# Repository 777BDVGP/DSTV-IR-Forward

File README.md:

# IR Forward — DSTV remote control in another room

Use your DSTV remote in a bedroom while the decoder is in another room. A
small board in the bedroom picks up the remote's infrared signal and sends it
over WiFi (ESP-NOW, board to board) to a board at the decoder, which sends it
out again on an infrared LED in front of the decoder.

**Project page:** https://zanaz.co.za/project-irforward.html — photos, build guide,
downloads and a contact form for questions.

### Why this project: only DSTV gets through

There are many ways to carry infrared from one room to another — IR repeaters,
"remote extenders", smart IR blasters. They pass on **every** infrared signal
they see. In a house with several TVs, sound bars and air conditioners that is
a problem: the bedroom TV remote also switches the lounge TV of the same
brand, the bedroom sound bar remote changes the lounge sound bar's volume, and
so on.

**This system deliberately blocks every remote except the DSTV remote.**

- The sender decodes each infrared signal it receives. Only signals in the
  **DSTV protocol (XMP)** are passed on; everything else — TV, sound bar,
  aircon, other set-top boxes — is ignored. The LEDs show it: **green** = DSTV
  code forwarded, **red** = other remote, ignored.
- The receiver does not replay a recording of the signal: it **rebuilds the
  DSTV code with exact timing**, so the decoder gets a clean signal even when
  the bedroom reception was weak.
- Result: you can use all your remotes normally in every room, and only the
  DSTV decoder reacts to the bedroom DSTV remote.
- Not DStv? The sender can **learn another TV box's remote** instead — see
  *Another TV box*.

The only exception is on purpose and temporary: while you **record an IR
sequence** from a sender's web page, that sender also passes on other remotes,
so you can see on the receiver's side that the recorded button works.

Extras on the receiver: record **IR sequences** from any remote (TV, sound
bar, DSTV), add known codes (e.g. Samsung TV Power ON / OFF), and run them on a
**weekly schedule** — for example a daily "reset" of TV, decoder and sound bar.

| Folder | Firmware | Where the board goes |
|---|---|---|
| `TV_IR_Sending` | **Sender (TX)** — one per room with a remote | in the room, IR receiver facing the remote |
| `TV_IR_Receiving` | **Receiver (RX)** — one per decoder | at the decoder, IR LED pointed at it |
| `TV_IR_IN_ONE` | **All-in-One** — sender and receiver on one board | when the remote's room and the decoder are next to each other (IR LED wired through) |

All three run on the same PCB (`PCB/IR_FORWARD_V1`), with a WEMOS LOLIN S2 Mini
(ESP32-S2). Printable enclosure parts (.stl: case, lid, IR clip, LED holders)
are in `Enclosure/`; the PCB (schematic, board, Gerber zip) is in `PCB/`.

**Firmware on a new board in 2 minutes, from the browser** — the normal way,
no software to install: https://777bdvgp.github.io/DSTV-IR-Forward/ (Chrome or
Edge) — see step 6 below.

## Building one, step by step

### 1. Order the PCB

Upload `PCB/IR_FORWARD_V1_2026-10-04.zip` (the Gerber files) to [PCBWay](https://www.pcbway.com/)
— I have my own boards made there and can recommend them: easy to order, good quality and
quick delivery — or any other PCB maker: 2 layers, 1.6 mm, default settings. The same PCB is
used for the sender, the receiver and the All-in-One. The Eagle schematic and
board are in `PCB/` (also as `SCHEMATIC.jpg` and `PCB.jpg`).

The finished PCB (S2 Mini not plugged in):

The **WEMOS LOLIN S2 Mini** (ESP32-S2) that plugs onto it — purple, with a
USB-C plug and the two buttons **0** (left) and **RST** (right) that you need
to put the firmware on it (step 6):

### 2. Parts on the PCB

| Qty | Part | Value / type | Silkscreen |
|---|---|---|---|
| 1 | WEMOS LOLIN **S2 Mini** (ESP32-S2) + 2 × **female** headers | plugs onto the two double pin rows | WEMOS MINI |
| 1 | AC/DC power module | **MORNSUN LD05-23B05R2-M** (100–277 V AC → 5 V) | MORNSUN |
| 1 | Voltage regulator | **AMS1117-3.3**, SOT-223 | 3.3VOLT |
| 2 | NPN transistor | **2N2222**, TO-92 | 2N2222 |
| 3 | Electrolytic capacitor | 220 µF, 16 V | C2, C3, C6 |
| 2 | Capacitor | 0.1 µF | C1, C5 |
| 4 | Resistor, through-hole | **130 Ω**, ¼ W (one per IR LED output) | U$2, U$3, U$5, U$7 |
| 1 | Resistor SMD 0805 | 2.2 kΩ | R1 |
| 2 | Resistor SMD 0805 | 330 Ω | R2, R5 |
| 1 | Resistor SMD 0805 | 4.7 kΩ | R48 |
| 1 | Screw terminal, 5.08 mm, 2-pole | mains in | 220VAC IN |
| 3 | Pin header 3-pin, 2.54 mm | TSOP, IR LEDs, red/green LED | TSOP31238, IR OUT, RED LED GREEN |
| 1 | Pin header 2-pin, 2.54 mm — **optional, may stay empty** | spare input, not used (see below) | INPUT |
| 2 | Pin header 2-pin + jumper | S2 Mini power: fit **LINK 5V**, leave **LINK 3.3V** open | LINK 5V, LINK 3.3V |

All headers are plain 2.54 mm (0.1", DuPont) — the cables use DuPont plugs.

**INPUT header — spare:** it is wired to the S2 Mini (GPIO 6, shorted to GND
= on), but no firmware uses it — nothing happens when it is switched. It is
there for a future idea; you can leave the header off the board.

**Surge protection (optional):** these parts only protect the board against
mains surges and let the firmware watch that protection. You can leave them
all out — the buzzer too, because it is only used to tell you that the
surge protection (TMOV) has blown:

| Qty | Part | Value / type | Silkscreen |
|---|---|---|---|
| 1 | Thermal MOV | **Littelfuse TMOV20RP275E** | LITLE_FUSE |
| 1 | Optocoupler | **4N35**, DIP-6 | OK1 |
| 1 | Diode | **M7** (1N4007), SMD | M7 |
| 1 | LED SMD 0805 | | LED1 |
| 5 | Resistor SMD 1206 | 10 kΩ | R10–R14 |
| 1 | Pin header 2-pin + jumper | jumper fitted (off = test "blown") | FUSE_LINK |
| 1 | Buzzer | **active** buzzer, **5 V**, 12 mm — only sounds when the TMOV has blown | BUZZER |

Left them out? Untick **Surge protection parts fitted (TMOV, 4N35)** on the
board's *Settings* page once after the first setup. The status then shows
*not fitted* and the buzzer stays quiet. Until you do, the board reports the
surge protection as **BLOWN** and the buzzer beeps every 2 seconds. With the
parts fitted, the board checks them all the time: a blown TMOV gives that
alarm (status **BLOWN**, buzzer beeps). Meanwhile you can switch the buzzer
off with the tick box **Mute buzzer - MOV blown** on the *Settings* page
until the TMOV is replaced.

**110–120 V countries (USA, Canada, Japan …):** the MORNSUN module works on
100–277 V, 50 or 60 Hz, so it stays the same — the "220VAC" on the PCB is only
printing. Two surge protection parts are made for 230 V:

- **TMOV:** use the 120 V version **Littelfuse TMOV20RP140E** (same size and
  footprint). The 275 V one is safe on 120 V but hardly protects.
- **4N35 monitor** (5 × 10 kΩ): on 120 V the 4N35 gets about half the current.
  It should still see the mains pulses — not tested. If the status shows
  **BLOWN** with a good TMOV, use 5 × 4.7 kΩ instead.

Or leave the surge protection out and untick *Surge protection parts fitted*.

### 3. Parts on cables (off the PCB)

| Part | Sender | Receiver | All-in-One | Connects to |
|---|:-:|:-:|:-:|---|
| **TSOP31238** IR receiver (38 kHz) | yes | optional (to record sequences on the receiver itself) | yes | TSOP31238 |
| **IR LED** 940 nm, e.g. TSAL6200 — 1 to 4 | — | yes | yes | IR OUT |
| **Red** and **green** 5 mm LED | yes | optional | yes | RED LED GREEN |
| Mains cable with plug | yes | yes | yes | 220VAC IN |

The red / green LEDs show what happens to each IR signal: on a sender
**green** = DSTV code forwarded, **red** = other remote, ignored.

### 4. Enclosure

3D-printable parts are in `Enclosure/` (.stl), printed in **PLA**. Pick the
case for how the board will be placed:

| Board | Print | Placement |
|---|---|---|
| Sender, box visible | `Case.stl` + `IR_Clip.stl` | the IR receiver (TSOP) is clipped on the inside of the box, at the side |
| Sender, box hidden | `Case2.stl` + `RoomLEDHolder.stl` | the box is hidden; the IR receiver and the red / green LEDs sit in the holder, mounted in the frame of the TV stand |
| Receiver | `Case3.stl` | hidden (e.g. in the roof), with wires out to **2 IR LEDs** pointed at the DSTV decoder |

Extra parts in the folder: `Lid`, `Angle`, `RoomLEDSupr`.

**Fixing the PCB in the case.** Two ways, use whichever you have:

- **Brass inserts (optional):** press threaded brass heat-set inserts into
  the posts in the case with a hot soldering iron, then screw the PCB down
  onto them from the inside.
- **No inserts?** Use ordinary **countersunk screws from the bottom**: put
  each screw in from under the case, through the countersunk hole, so its
  head sits flush with the bottom, and use it to hold the PCB down in the case.

### 5. Assembly

1. Solder the SMD parts first (resistors, AMS1117, and the optional M7 /
   LED1 / 10 kΩ), then the low through-hole parts, then the tall ones
   (capacitors, buzzer, terminal, MORNSUN, TMOV).
2. Mind the polarity of the electrolytic capacitors, the 2N2222s, the 4N35
   (pin 1 dot), the buzzer (+) and the diode.
3. Solder the female headers to the **S2 Mini**, so it plugs onto the PCB and
   can be taken off.
4. Fit the **LINK 5V** jumper (not LINK 3.3V), and FUSE_LINK if the surge
   parts are fitted.
5. Make the cables for the TSOP, the IR LED(s) and the red / green LEDs with
   2.54 mm DuPont plugs.
6. **Before connecting mains:** flash the firmware over USB (next section) —
   the S2 Mini gets its power from USB then. Program it **off** the board or
   with the mains disconnected.

**Safety:** the PCB carries mains voltage (230 V or 120 V). Never touch the board while it is
connected to mains, and always fit it in its closed enclosure. Have the mains
wiring checked by a qualified person.

### 6. Put the firmware on the S2 Mini

**The normal way is A, the Install page in the browser** — nothing to
install, and it takes about 2 minutes. Use B only if you are a developer who
wants to change the code.

| | **A. In the browser** | **B. With PlatformIO** |
|---|---|---|
| For | everyone who just wants it running | developers who want to change the code |
| You need | Chrome or Edge on a PC / Mac | VS Code + PlatformIO, about 1 GB of tools |
| Time | about 2 minutes | about 20 minutes the first time |

Both need a **USB-C data cable** (some cables only charge). Flash the S2 Mini
**off the PCB**, or with the mains disconnected — it gets its power from USB.
The buttons **0** and **RST** are at the top, left and right of the USB-C plug
(see the S2 Mini photo in step 1).

#### A. In the browser — the normal way (no software to install)

1. Open the **Install page** of this project in **Chrome** or **Edge**
   — **https://777bdvgp.github.io/DSTV-IR-Forward/** (the page is `docs/index.html`).
2. Plug in the S2 Mini. Hold button **0**, tap **RST**, let go of **0**.
3. Click **Sender**, **Receiver** or **All-in-One**, pick the port in the
   pop-up (often `ESP32-S2`), then **Install**. Answer **Erase** with yes for a
   new board. It takes about a minute.
4. Tap **RST**. The board starts its setup WiFi — go on with *First setup*.
   (If the page says it cannot connect after the install: normal — the S2
   Mini cannot restart itself over USB; the firmware is written.)

Without the Install page: download `sender.bin`, `receiver.bin` or
`allinone.bin` from `docs/firmware/` and flash it with the
[Espressif web flasher](https://espressif.github.io/esptool-js/) — *Connect*,
**Flash Address `0x0`**, choose the file, *Program*.

#### B. With PlatformIO (only for developers)

1. Install [Visual Studio Code](https://code.visualstudio.com), then in VS
   Code *Extensions* → **PlatformIO IDE**.
2. Download this project (*Code → Download ZIP*, or `git clone`) and unzip it.
3. *File → Open Folder* → the folder of the firmware you want, e.g.
   `TV_IR_Receiving` (that folder itself, not the top folder). The first build
   downloads the ESP32 tools and libraries by itself (a few minutes).
4. Plug in the S2 Mini, hold button **0**, tap **RST** (download mode).
5. Flash over USB:
   - Sender: `pio run -e usb -t upload`
   - Receiver: `pio run -e rx_usb -t upload`
   - All-in-One: `pio run -e usb -t upload`
6. Press **RST**. (The upload may report "failed" only because the S2 cannot
   be reset over USB — the firmware is written.)

Every build also writes two files to the project's `firmware_out/`:
`<project>_v<version>.bin` (updates over WiFi) and `<project>_v<version>_full.bin`
(a whole new board, flashed at address `0x0` — what the Install page uses).
To refresh the Install page after a new version: build the three projects,
run `python docs/update_firmware.py`, commit `docs/`. Built with your own
`src/Private.h`, the file is named `..._full_PRIVATE.bin` and the script
leaves it out — never share that one.

## First setup (once per board)

A new board has no WiFi settings. It opens its own **setup WiFi**:
`IR-FORWARD-TX-xxxx`, `IR-FORWARD-RX-xxxx` or `IR-FORWARD-IN1-xxxx` (open, no
password). The red and green LEDs blink alternately.

1. Join that WiFi with a phone. The setup page opens (or go to `http://192.168.4.1`).
2. Pick your home WiFi, enter its password.
3. IP address: tick **automatic (DHCP)**, or enter a fixed IP.
4. **Channel lock** — see *WiFi channel* below. In short:
   - **receiver**: **Any channel** (one router or a mesh system)
   - **sender**: **Follow receiver** (already selected on a new sender)
5. **Choose an owner password** (6+ characters) and keep it safe. You need it
   to change the WiFi settings later and for every firmware update.
6. Save. The board restarts and joins your WiFi.

The setup WiFi comes back by itself if the board cannot connect 3 times in a
row (and leaves again after 5 minutes to retry), or when you hold button **0**
for 5 seconds (WiFi settings deleted). Saving there always needs the owner
password, so a neighbour joining the setup WiFi cannot change anything.

### How to open the board's page

| Address | When |
|---|---|
| `http://192.168.4.1` | **Only during setup**: your phone must be connected to the board's own setup WiFi `IR-FORWARD-…`. It stops working once the board has joined your home WiFi. |
| `http://192.168.1.xxx` (the board's IP) | **Normal use**, on your home WiFi. Works on every phone and PC. Find the IP in your router's list of connected devices. |
| `http://<host name>.local` | **Normal use** too, e.g. `http://ir-tx-9e80.local`. The host name is `ir-` + `tx` / `rx` / `in1` + the last 4 characters of the setup WiFi name (you can change it on the setup page). Works on PCs and iPhones; many Android phones do not support `.local`, so use the IP there. |

If you only see the setup page at `192.168.4.1` while you expected your home
WiFi, the board could not join it — usually a typo in the WiFi password. Set
it up again and watch out for the phone's automatic capital first letter.

## WiFi channel

The senders talk to the receiver directly over the air (ESP-NOW), not through
your router. That only works when they are all on the **same WiFi channel**.
The **receiver** decides the channel; senders set to **Follow receiver** find
it by themselves.

| Your WiFi | Receiver: Channel lock | Senders: Channel lock |
|---|---|---|
| One router | Any channel | Follow receiver |
| Mesh system (TP-Link Deco, Google / Nest WiFi, Eero …) | Any channel | Follow receiver |
| Several separate access points on different channels | Any channel, or a fixed channel (see *Several access points*) | Follow receiver |

**How "Follow receiver" works:** the sender remembers the channel on which it
hears the receiver, also after a restart. If it hears nothing from the
receiver for 5 minutes (for example because the router changed channel), it
leaves the WiFi for about 30 seconds, listens on channels 1 to 13 for the
receiver, and restarts on the channel where it found it. If the receiver is
not found (switched off?), it waits longer before the next try — 10, 20, 40,
up to 80 minutes — and goes back to its normal WiFi meanwhile.

The All-in-One has no channel setting: it does not use ESP-NOW.

## Using it

Open the board's IP (or `http://<host name>.local`) in a browser.

- **Sender**: status, link to the receiver, settings, and **IR SEQUENCES** —
  record a sequence by pointing a remote at this board.
- **Receiver**: status of all senders, **IR SEQUENCES** (run, edit, add known
  codes such as Samsung TV Power ON/OFF) and **SCHEDULE** (run sequences at set
  times; per line: on/off, × repeats, every … ms, pause after).
- **All-in-One**: status, **IR SEQUENCES** with the schedule (as on the
  receiver; record by pointing a remote at this board) and **SETTINGS**
  (forwarding on/off, *Forward remote* / *Learn remote*, *Echo guard*).
- **WIFI** page on every board. Sender and receiver also have `/wifiscan`:
  which access points the board hears, on which channel and how strong.

### All-in-One: Echo guard

The All-in-One receives the remote on its IR eye and sends it out again on its
IR LED. If the eye can **see its own IR LED** (same room, or a reflection off
a wall or window), it picks up its own signal and sends it again — the decoder
gets every button two or more times. The **Echo guard** (Settings) stops that:
it ignores everything the eye receives while the LED sends and for 150 ms
after.

| Where is the IR LED? | Echo guard |
|---|---|
| In another room, or the eye cannot see it | **off** (default) |
| The eye can see the LED | **on** |

Leave it off when you can: held buttons (volume, scrolling channels) send a
repeat every ~80 ms, and with the guard on those repeats are thrown away.

Test: press one DStv button once and watch the green LED — **one** flash is
right; several flashes for one press means an echo → switch the guard on.

## Another TV box (not DStv)

Out of the box only the DStv remote is forwarded. For another TV box —
Sky, Foxtel, a cable or satellite box, a Freeview box … — teach the sender
(or the All-in-One) that box's remote:

1. Open the board's **Settings** page.
2. Tick **Learn remote**, press **UPDATE**.
3. Point the TV box's remote at the board and press one button (shortly).
4. **Forward remote** now shows that remote, e.g. `NEC 0x20DF`, and
   *Learn remote* is unticked again. From now on only that remote is
   forwarded — green LED; every other remote is ignored — red LED.

Back to DStv: type `XMP` in **Forward remote** and press **UPDATE**. You can
also type a remote yourself: a protocol name (`NEC`, `SAMSUNG`, `RC5`, `RC6`,
`SONY`, `PANASONIC`, …), optionally followed by the address of that remote.

Good to know:
- A DStv code is rebuilt with exact timing. Other remotes are passed on as the
  timing the board received — that works for most remotes, but test it.
- Remotes with very long codes (more than 100 pulses) cannot be forwarded,
  and remotes that use Bluetooth or radio instead of infrared (e.g. Sky Q,
  Apple TV) cannot be used at all.
- With several senders, teach each sender the same remote.

## Firmware updates over WiFi

The owner password protects network updates. Set it once on your PC as the
environment variable `IR_OTA_PASS`, e.g. on Windows:

```
setx IR_OTA_PASS your-owner-password
```

(open a new terminal afterwards), then:

```
pio run -e ota -t upload --upload-port <board ip>        (sender, All-in-One)
pio run -e rx_ota -t upload --upload-port <board ip>     (receiver)
```

Own upload targets: copy `private.example.ini` to `private.ini` (not committed)
and add `[env:...]` sections with your boards' IPs.

All-in-One without PlatformIO: build, then upload
`firmware_out/TV_IR_IN_ONE_v<version>.bin` on `http://<board ip>/update`.

Forgot the owner password? Erase the board over USB
(`pio run -e usb -t erase`, receiver: `-e rx_usb`) and flash again; then do
the first setup again.

## Several access points

With several access points on different channels, each board joins the one it
hears best — possibly on different channels. "Follow receiver" keeps the
senders with the receiver, but each sender also needs an access point **on
the receiver's channel** for its own WiFi (web page, updates). So choose the
receiver's channel with care:

1. Fix the 2.4 GHz channel of your access points (not *Auto*), so it does not
   change by itself.
2. Open `/wifiscan` on every board (WIFI page → *Which access points does this
   board hear?*) and pick the channel that **every** board hears well (better
   than about -70 dBm). Several access points on that one channel are fine.
3. Receiver: set **Channel lock** to that channel. Senders: **Follow receiver**
   (or the same channel number).
4. If your WiFi system can lock clients to access points (e.g. TP-Link Omada
   "Lock to wireless device"), allow only the access points on that channel —
   **after** step 3, otherwise the boards lose WiFi until they restart.

## Troubleshooting

- **A sender shows *offline* on the receiver's status page**, although it is
  powered and its own web page opens: it is on a different WiFi channel than
  the receiver. With *Follow receiver* it searches by itself within 5 minutes
  (its log says "searching channels 1-13" and "Receiver found on channel …").
  With a fixed channel: check the Channel lock of both boards, and `/wifiscan`.
- **A sender's web page does not open after it followed the receiver:** there
  is no access point on the receiver's channel that this sender can hear — see
  *Several access points*.
- **The red and green LEDs blink alternately:** the board is in its setup WiFi
  (it could not join your WiFi 3 times). It retries your WiFi after 5 minutes;
  to change the settings, join `IR-FORWARD-…` with a phone.
- **"Authentication Failed" on a network upload:** `IR_OTA_PASS` is not set,
  or not to this board's owner password. Open a new terminal after `setx`.

## Optional: `src/Private.h`

Building several boards for yourself? Copy `src/Private.example.h` to
`src/Private.h` (never committed) to pre-load the owner password, your access
point names and (All-in-One) your WiFi networks into every board you flash.

## Licence

Copyright (c) 2026 Bennie Vermeulen. Licensed under
[CC BY-NC 4.0](https://creativecommons.org/licenses/by-nc/4.0/): you may use,
share and change it for **non-commercial** purposes, with credit to the author.
Selling the firmware, boards, enclosures or devices built from them is not
allowed. See `LICENSE`.

**Safety:** the board runs from mains voltage (230 V or 120 V). Building and installing it is at
your own risk — have mains wiring done or checked by a qualified person.

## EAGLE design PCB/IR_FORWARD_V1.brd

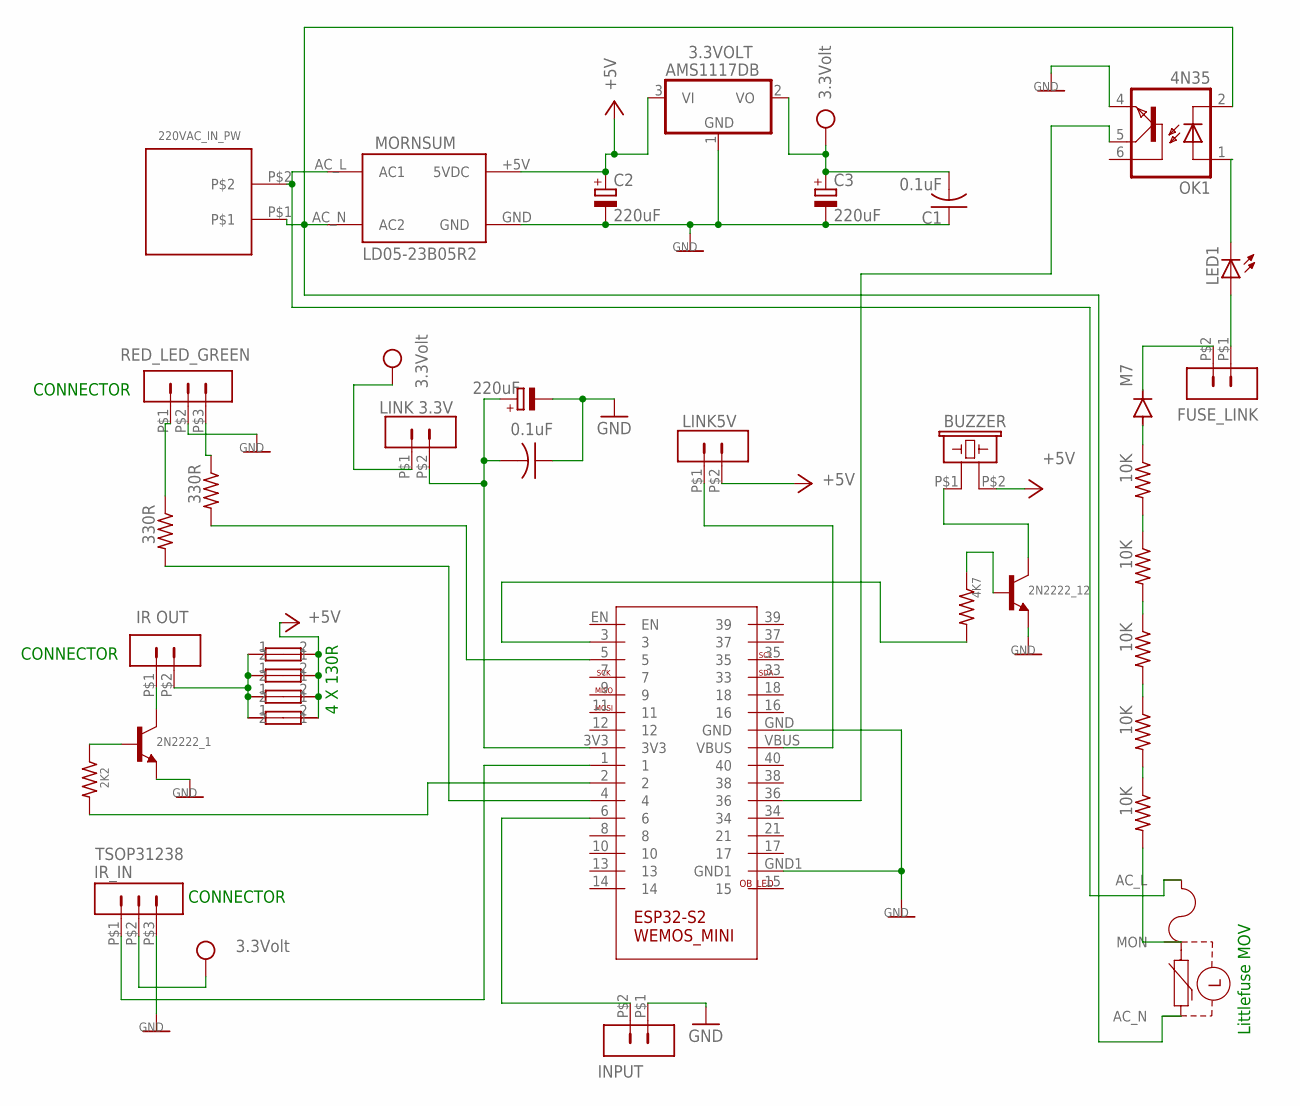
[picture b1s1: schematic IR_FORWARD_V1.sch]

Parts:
2N2222_1, 2N2222_12: 2N2222; TO92
3.3VOLT: AMS1117DB; SOT223
220VAC_SWITCH1: 220VAC_IN_PW; TERM-5.05-2
BUZZER: BUZZERDONUT; F/CM12P_2
C1, C5: 0.1uF; C050-025X075
C2, C3, C6: 220uF; E2,5-7
IR_IN: TSOP31238; 3WAY_SH_NARROW
LED1: LEDCHIPLED_0805; CHIPLED_0805
LINK5V: LINK5V; 2WAYNORMAL
M7-10: M7; SOD106-R
MORNSUM: MORNSUM_PSLONG; LD05-23B05R2-M
OK1: 4N35; DIL06
R1: 2K2; R0805
R2, R5: 330R; R0805
R10, R11, R12, R13, R14: 10K; R1206
R48: 4K7; R0805
U$1: RED_LED_GREEN; 3WAY_SH_NARROW
U$2, U$3, U$5, U$7: 130R; 0207/10
U$4: WEMOS_S2_MINI
U$6: INPUT; 2WAY_SH_NARROW
U$9: LITLE_FUSE
U$12: IR OUT; 2WAY_SH_NARROW
U$15: LINK 3.3V; 2WAYNORMAL
U$20: FUSE_LINK; 2WAYNORMAL

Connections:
+5V: 3.3VOLT.3 (VI), BUZZER.P$2 (2), C2.+, LINK5V.P$2 (2), MORNSUM.+5V (5VDC), U$2.2, U$3.2, U$5.2, U$7.2
GND: 2N2222_1.3 (E), 2N2222_12.3 (E), 3.3VOLT.1 (GND), C1.1, C2.-, C3.-, C5.1, C6.-, IR_IN.P$3 (3), MORNSUM.GND, OK1.4 (EMI), U$1.P$2 (2), U$4.GND, U$4.GND1, U$6.P$1 (1)
unnamed: LINK5V.P$1 (1), U$4.VBUS
unnamed: 2N2222_12.2 (B), R48.1
unnamed: U$2.1, U$3.1, U$5.1, U$7.1, U$12.P$2 (2)
unnamed: R2.1, U$1.P$3 (3)
unnamed: R2.2, U$4.5
unnamed: 220VAC_SWITCH1.P$1, MORNSUM.AC_N (AC2), OK1.2 (C), U$9.AC_N
unnamed: R5.1, U$1.P$1 (1)
unnamed: 220VAC_SWITCH1.P$2, MORNSUM.AC_L (AC1), U$9.AC_L
unnamed: R11.2, R12.1
unnamed: R5.2, U$4.4
unnamed: U$4.6, U$6.P$2 (2)
unnamed: 2N2222_1.2 (B), R1.1
unnamed: C5.2, C6.+, U$4.3V3, U$15.P$2 (2)
unnamed: R1.2, U$4.2
unnamed: 2N2222_1.1 (C), U$12.P$1 (1)
unnamed: 2N2222_12.1 (C), BUZZER.P$1 (1)
unnamed: IR_IN.P$1 (1), U$4.1
unnamed: OK1.5 (COL), U$4.36
unnamed: LED1.C, OK1.1 (A)
unnamed: R10.1, R14.2
unnamed: R10.2, R11.1
unnamed: R48.2, U$4.3
unnamed: R12.2, R13.1
unnamed: LED1.A, U$20.P$1 (1)
unnamed: M7-10.A, R14.1
unnamed: M7-10.C, U$20.P$2 (2)
unnamed: R13.2, U$9.MON
VCC: 3.3VOLT.2 (VO), C1.2, C3.+, IR_IN.P$2 (2), U$15.P$1 (1)

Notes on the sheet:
4 X 130R
Littlefuse MOV
CONNECTOR

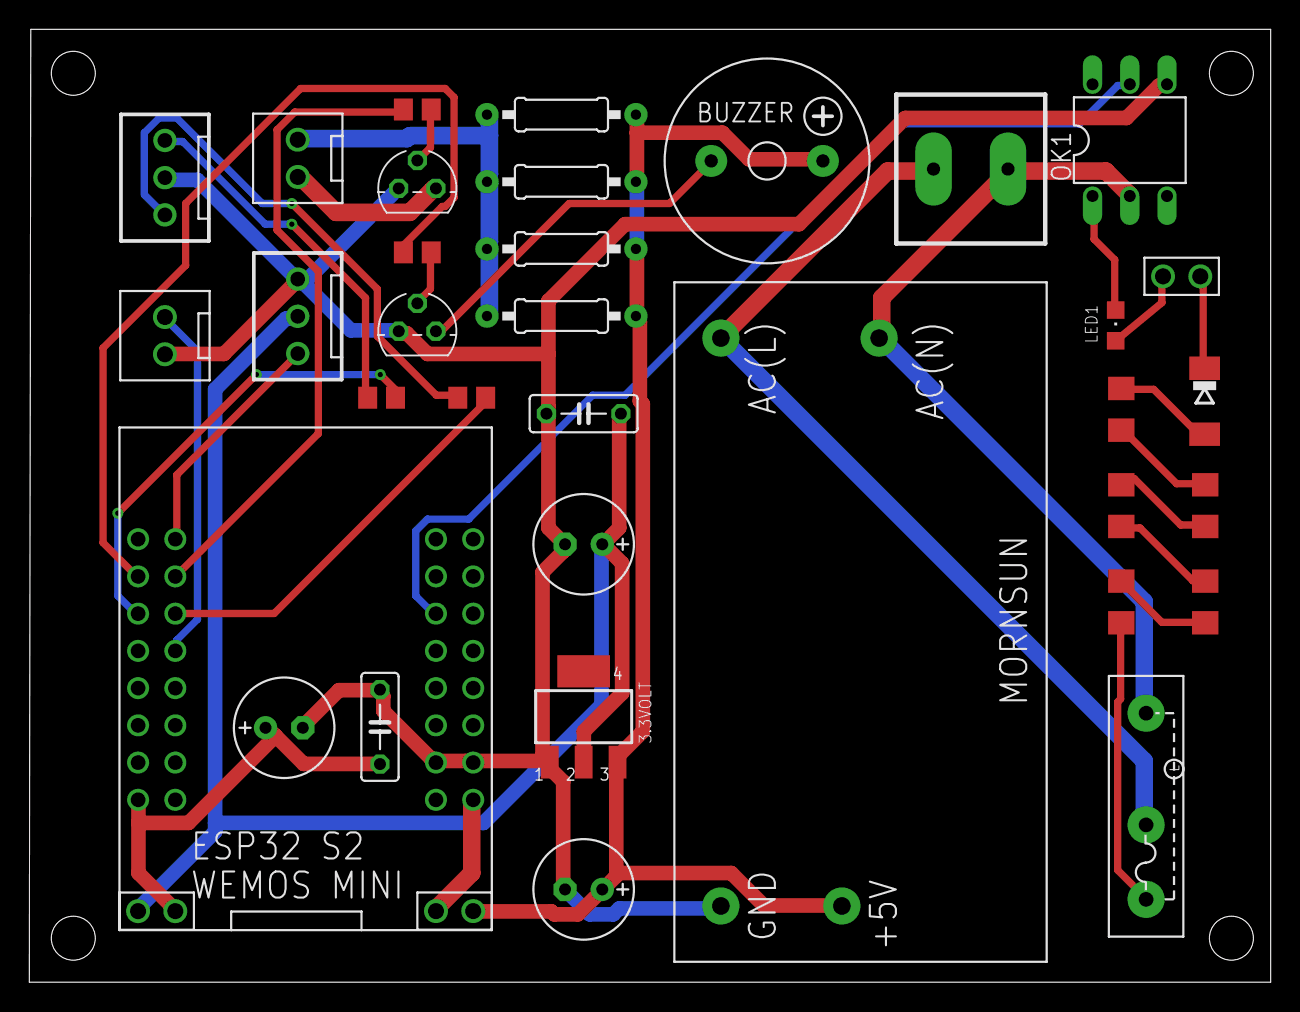
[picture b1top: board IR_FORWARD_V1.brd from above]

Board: 2 copper layers, 84.7 x 65.0 mm, 36 parts (0 on the bottom side), 30 nets.
